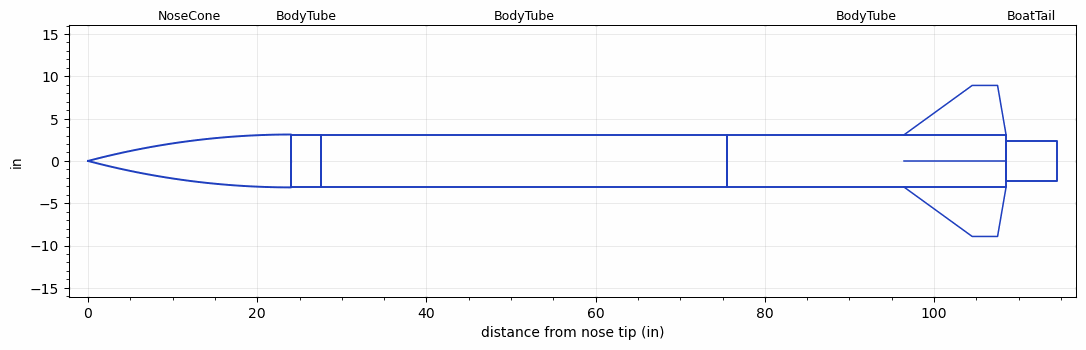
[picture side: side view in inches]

<RASAeroDocument>
 <FileVersion>2</FileVersion>
 <RocketDesign>
  <NoseCone>
   <Length>24</Length>
   <Diameter>6.25</Diameter>
   <Shape>Tangent Ogive</Shape>
   <Location>0</Location>
  </NoseCone>
  <BodyTube>
   <Length>3.5</Length>
   <Diameter>6.25</Diameter>
   <Location>24</Location>
  </BodyTube>
  <BodyTube>
   <Length>47.9999</Length>
   <Diameter>6.25</Diameter>
   <LaunchLugDiameter>0.3937</LaunchLugDiameter>
   <LaunchLugLength>0.5905</LaunchLugLength>
   <Location>27.4999</Location>
  </BodyTube>
  <BodyTube>
   <Length>32.9999</Length>
   <Diameter>6.25</Diameter>
   <LaunchLugDiameter>0.3937</LaunchLugDiameter>
   <LaunchLugLength>0.5905</LaunchLugLength>
   <Location>75.4998</Location>
   <Fin>
    <Count>4</Count>
    <Chord>12</Chord>
    <Span>5.8</Span>
    <SweepDistance>8.0017</SweepDistance>
    <TipChord>3</TipChord>
    <Thickness>0.25</Thickness>
    <Location>12</Location>
    <AirfoilSection>Rounded</AirfoilSection>
   </Fin>
  </BodyTube>
  <BoatTail>
   <Length>6</Length>
   <Diameter>4.75</Diameter>
   <RearDiameter>4.75</RearDiameter>
   <Location>108.4998</Location>
  </BoatTail>
  <Surface>Camouflage Paint</Surface>
  <CD>0</CD>
  <ModifiedBarrowman>False</ModifiedBarrowman>
  <Turbulence>False</Turbulence>
  <UseBooster1>False</UseBooster1>
  <UseBooster2>False</UseBooster2>
 </RocketDesign>
 <LaunchSite>
  <Altitude>4995.0002</Altitude>
  <Pressure>24.9023</Pressure>
  <RodAngle>5</RodAngle>
  <RodLength>137.9997</RodLength>
  <Temperature>41.187</Temperature>
  <WindSpeed>15</WindSpeed>
 </LaunchSite>
 <Recovery>
  <Altitude1>1000</Altitude1>
  <Altitude2>0</Altitude2>
  <DeviceType1>Parachute</DeviceType1>
  <DeviceType2>None</DeviceType2>
  <Event1>True</Event1>
  <Event2>False</Event2>
  <Size1>143.9997</Size1>
  <Size2>0</Size2>
  <EventType1>Altitude</EventType1>
  <EventType2>None</EventType2>
  <CD1>0.97</CD1>
  <CD2>0</CD2>
 </Recovery>
 <SimulationList>
  <Simulation>
   <SustainerEngine>M2500T  (AT)</SustainerEngine>
   <SustainerLaunchWt>70.5959</SustainerLaunchWt>
   <SustainerCG>70.147</SustainerCG>
   <SustainerIgnitionDelay>0</SustainerIgnitionDelay>
   <Booster1SeparationDelay>0</Booster1SeparationDelay>
   <Booster1IgnitionDelay>0</Booster1IgnitionDelay>
   <IncludeBooster1>False</IncludeBooster1>
   <Booster2Delay>0</Booster2Delay>
   <IncludeBooster2>False</IncludeBooster2>
  </Simulation>
  <Simulation>
   <SustainerEngine>M2500T  (AT)</SustainerEngine>
   <SustainerLaunchWt>70.5959</SustainerLaunchWt>
   <SustainerCG>70.147</SustainerCG>
   <SustainerIgnitionDelay>0</SustainerIgnitionDelay>
   <Booster1SeparationDelay>0</Booster1SeparationDelay>
   <Booster1IgnitionDelay>0</Booster1IgnitionDelay>
   <IncludeBooster1>False</IncludeBooster1>
   <Booster2Delay>0</Booster2Delay>
   <IncludeBooster2>False</IncludeBooster2>
  </Simulation>
  <Simulation>
   <SustainerEngine>M2500T  (AT)</SustainerEngine>
   <SustainerLaunchWt>70.5959</SustainerLaunchWt>
   <SustainerCG>70.147</SustainerCG>
   <SustainerIgnitionDelay>0</SustainerIgnitionDelay>
   <Booster1SeparationDelay>0</Booster1SeparationDelay>
   <Booster1IgnitionDelay>0</Booster1IgnitionDelay>
   <IncludeBooster1>False</IncludeBooster1>
   <Booster2Delay>0</Booster2Delay>
   <IncludeBooster2>False</IncludeBooster2>
  </Simulation>
  <Simulation>
   <SustainerEngine>M2500T  (AT)</SustainerEngine>
   <SustainerLaunchWt>70.5959</SustainerLaunchWt>
   <SustainerCG>70.147</SustainerCG>
   <SustainerIgnitionDelay>0</SustainerIgnitionDelay>
   <Booster1SeparationDelay>0</Booster1SeparationDelay>
   <Booster1IgnitionDelay>0</Booster1IgnitionDelay>
   <IncludeBooster1>False</IncludeBooster1>
   <Booster2Delay>0</Booster2Delay>
   <IncludeBooster2>False</IncludeBooster2>
  </Simulation>
 </SimulationList>
</RASAeroDocument>
